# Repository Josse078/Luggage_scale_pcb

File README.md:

# Portable Digital Luggage Scale PCB

Custom 2-layer printed circuit board (PCB) design for a portable digital luggage scale, created using **KiCad**.

## 📌 Overview
This project integrates an Arduino microcontroller, load cell amplifier module, OLED display, and a LiPo power management circuit into a compact custom PCB layout.

---

## 🛠️ Hardware & Components
* **MCU:** Arduino Nano / Nano Every
* **Weight Sensor Interface:** HX711 Load Cell Amplifier
* **Display:** 0.96" I2C OLED Display (128x64)
* **Power Management:** 3.7V LiPo Battery, TP4056 Charger + 5V Boost Converter Module
* **Controls:** 
  * SPDT Slide Switch (Main Power On/Off)
  * Tactile Pushbutton (Tare / Zero Scale)

---

## 📐 PCB Layout & Design Highlights
* **Modular Interconnects:** Utilizes 4-pin headers/connectors for off-board modules (Display, HX711, Power) to simplify assembly and maintenance.
  
---

## 📁 Files & Repository Structure
* `Luggage_Scale.kicad_sch` – Schematic source file
* `Luggage_Scale.kicad_pcb` – PCB layout source file
* `*.gbr` – Output Gerber layers (`F.Cu`, `B.Cu`, `F.Silkscreen`, `B.Silkscreen`, `F.Mask`, `B.Mask`, `Edge.Cuts`)
* `*.drl` – Excellon drill files (`PTH` and `NPTH`)
* `Luggage_Scale-job.gbrjob` – Gerber job file

---

## 🚀 Manufacturing
Gerber and drill files are generated and ready for direct upload to PCB fabrication services (JLCPCB, PCBWay, etc.).

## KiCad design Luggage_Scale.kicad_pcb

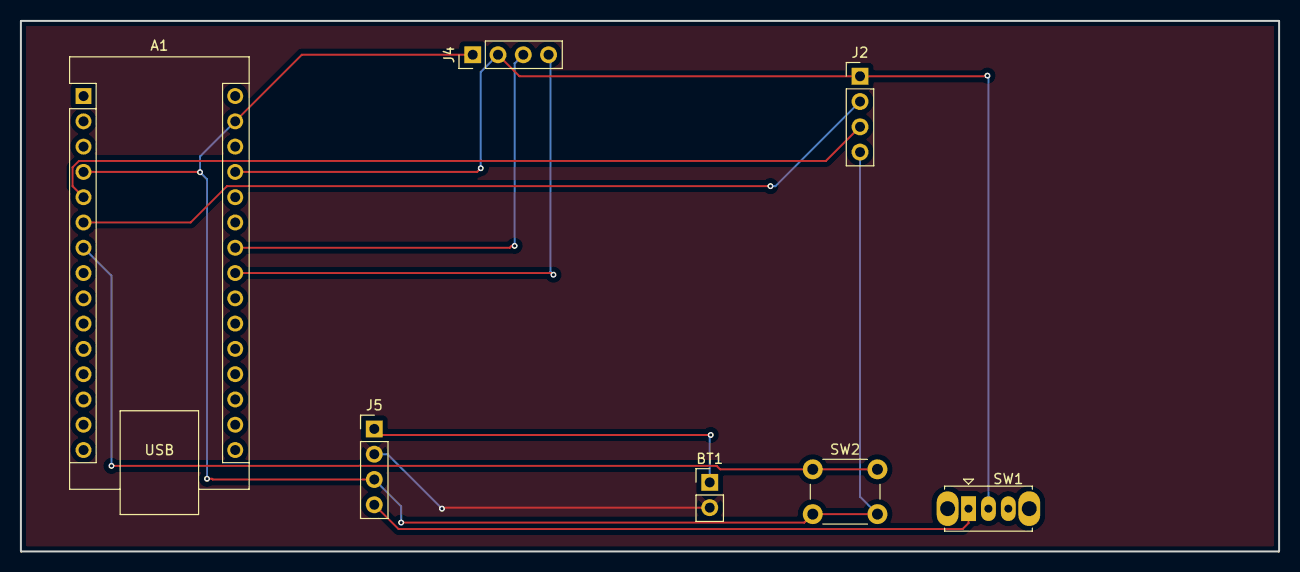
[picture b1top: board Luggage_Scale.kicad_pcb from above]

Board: 2 copper layers, 126.4 x 53.3 mm, 7 parts (0 on the bottom side), 10 nets.

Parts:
A1: Arduino_Nano_Every; Arduino_Nano
BT1: 3.7V LiPo Battery; PinHeader_1x02_P2.54mm_Vertical
J2: HX711; PinHeader_1x04_P2.54mm_Vertical
J4: OLED Display (0.96" I2C); PinHeader_1x04_P2.54mm_Vertical
J5: TP4056 + 5V Boost Module; PinHeader_1x04_P2.54mm_Vertical
SW1: SW_SPDT; SW_Slide_SPDT_Straight_CK_OS102011MS2Q
SW2: Tare Pushbutton; SW_PUSH_6mm_H5mm

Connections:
unnamed: A1.27 (+5V), J2.1, J4.2, SW1.2 (B)
unnamed: A1.5 (D2), J2.3
unnamed: A1.6 (D3), J2.2
unnamed: A1.7 (D4), SW2.1
unnamed: A1.24 (SCL/A5), J4.3
unnamed: A1.23 (SDA/A4), J4.4
unnamed: BT1.1 (+), J5.1 (VIN+)
unnamed: BT1.2 (-), J5.2 (VIN-)
unnamed: A1.4 (GND), A1.29 (GND), J2.4, J4.1, J5.3 (BAT+), SW2.2
unnamed: J5.4 (BAT-), SW1.1 (A)
